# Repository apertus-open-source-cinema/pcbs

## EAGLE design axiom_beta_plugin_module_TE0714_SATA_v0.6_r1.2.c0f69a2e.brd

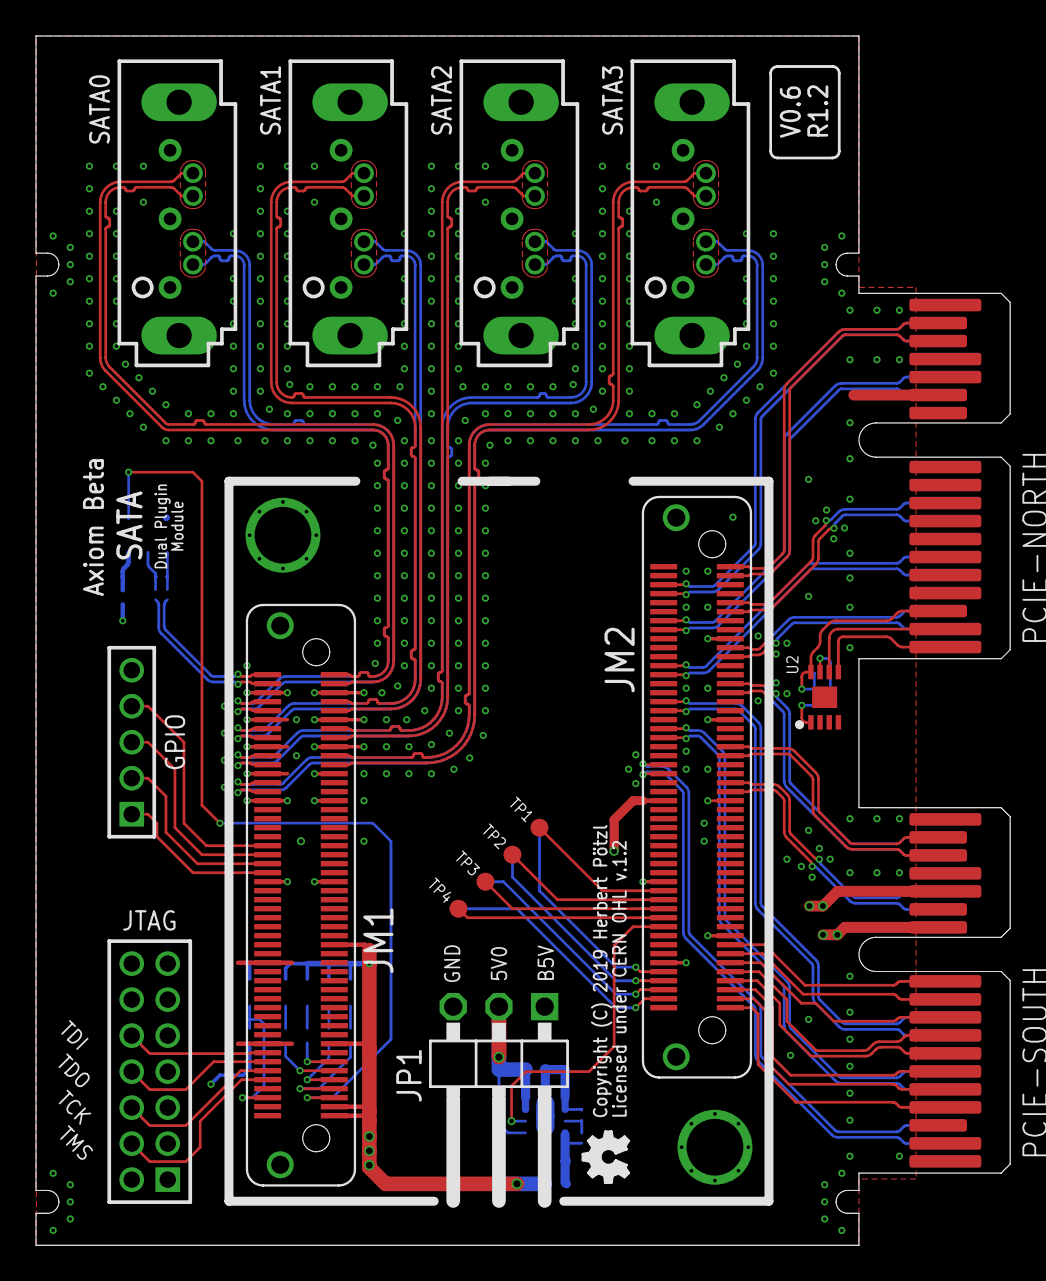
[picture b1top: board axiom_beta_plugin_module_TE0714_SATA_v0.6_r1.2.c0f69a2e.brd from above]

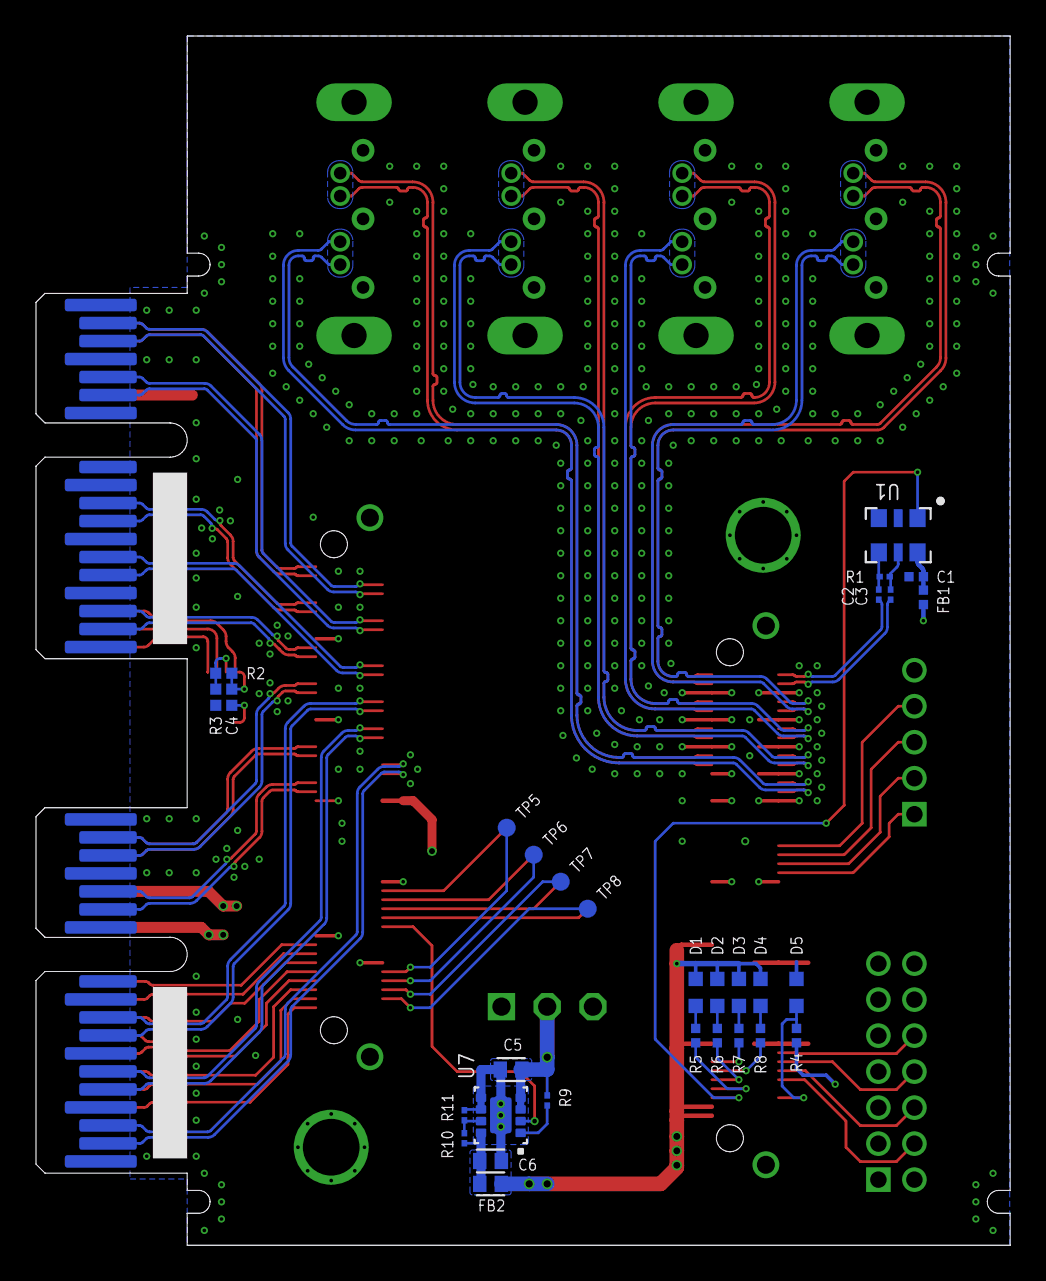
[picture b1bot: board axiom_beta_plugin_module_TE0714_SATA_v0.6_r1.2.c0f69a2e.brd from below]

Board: 4 copper layers, 54.1 x 67.2 mm, 47 parts (30 on the bottom side), 93 nets.

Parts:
C1: 470n; 0402-C
C2, C3: 100n; 0201-C
C4: 0402-B
C5: 10u; 0603-C
C6: 22u; 0603-C
D1, D2, D3, D4, D5: LED; CHIPLED_0603
FB1: 600R 500mA; 0402-C
FB2: 220R 2.2A; 0603-C
GPIO: MMTM-105-05; 1X05M
JM1, JM2: LSHM-150-XX.X-XX-DV-A-S
JP1: 22-28-8034; 1X03/90-S
JTAG: 87760-1416; 2X07M
LOGO2: OSHW_LOGO_FILLX0100-NT; OSHW_FILLX100_NOTEXT
PCIE-NORTH: PCIE-36-AXIOM
PCIE-SOUTH: PCIE-36-AXIOM
R1: 100R; 0201-C
R2: 10k; 0402-B
R3: 1k; 0402-B
R4: 5k6; 0402-C
R5, R6, R7, R8: 10k; 0402-C
R9: 10k; 0201-C
R10: 510k; 0201-C
R11: 162k; 0201-C
SATA0, SATA1, SATA2, SATA3: 67491-0025; SATA7-VERT-S
TP1, TP2, TP3, TP4, TP5, TP6, TP7, TP8: TPTP10R; TP10R
U1: DSC11XX-3.2X2.5; 3.2X2.5
U2: BR24G04NUX; DFN200X300X100-9N
U7: TPS82085; MICROSIP

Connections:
3V3: D1.A, D2.A, D3.A, D4.A, FB1.1, FB2.2, JM1.61, JM1.83, JM1.97, JM1.99, R4.2
B14_L0: JM2.99, PCIE-SOUTH.B4
B14_L11_N: JM2.74, TP1.TP
B14_L11_P: JM2.76, TP2.TP
B14_L12_P: JM2.82, U7.2
B14_L14_N: JM2.78, TP3.TP
B14_L14_P: JM2.80, TP4.TP
B14_L17_N: JM2.89, PCIE-SOUTH.B9
B14_L17_P: JM2.91, PCIE-SOUTH.B8
B14_L18_N: JM2.85, PCIE-SOUTH.B11
B14_L18_P: JM2.87, PCIE-SOUTH.B10
B14_L19_N: JM2.94, TP6.TP
B14_L19_P: JM2.92, TP5.TP
B14_L20_N: JM2.95, PCIE-SOUTH.B6
B14_L20_P: JM2.93, PCIE-SOUTH.B7
B14_L21_N: JM1.95, U1.1
B14_L21_P: JM1.93, R5.1
B14_L22_N: JM2.96, TP7.TP
B14_L22_P: JM2.98, TP8.TP
B14_L23_N: JM1.89, R8.1
B14_L23_P: JM1.91, R6.1
B14_L24_P: JM1.87, R7.1
B14_L25: JM2.97, PCIE-SOUTH.B5
B15_L1_N: JM2.14, PCIE-NORTH.A14
B15_L1_P: JM2.16, PCIE-NORTH.A13
B15_L5_N: JM2.8, PCIE-NORTH.A16
B15_L5_P: JM2.6, PCIE-NORTH.A17
B15_L6_N: JM2.26, PCIE-NORTH.A5
B15_L6_P: JM2.24, PCIE-NORTH.A6
B15_L7_N: JM2.1, PCIE-NORTH.B17
B15_L7_P: JM2.3, PCIE-NORTH.B16
B15_L10_N: JM2.11, PCIE-NORTH.A8
B15_L10_P: JM2.9, PCIE-NORTH.A9
B15_L12_N: JM2.34, PCIE-SOUTH.A8
B15_L12_P: JM2.32, PCIE-SOUTH.A9
B15_L13_N: JM2.38, PCIE-SOUTH.A6
B15_L13_P: JM2.40, PCIE-SOUTH.A5
B15_L15_N: JM2.19, PCIE-NORTH.A3
B15_L15_P: JM2.21, PCIE-NORTH.A2
B15_L18_N: JM2.27, PCIE-SOUTH.A17
B15_L18_P: JM2.29, PCIE-SOUTH.A16
B15_L19_N: JM2.41, PCIE-SOUTH.B17
B15_L19_P: JM2.43, PCIE-SOUTH.B16
B15_L22_N: JM2.46, PCIE-SOUTH.A3
B15_L22_P: JM2.48, PCIE-SOUTH.A2
B15_L23_N: JM2.51, PCIE-SOUTH.A13
B15_L23_P: JM2.49, PCIE-SOUTH.A14
B34_L3_N: GPIO.3, JM1.42
B34_L3_P: GPIO.4, JM1.40
B34_L9_N: GPIO.1, JM1.46
B34_L9_P: GPIO.2, JM1.44
DONE: D5.A, JM1.96, R4.1
EN_B: R9.1, U7.1
FB_B: R10.1, R11.2, U7.7
GND: C1.2, C4.2, C5.2, C6.2, D5.C, GPIO.5, JM1.5, JM1.6, JM1.11, JM1.12, JM1.17, JM1.18, JM1.23, JM1.24, JM1.29, JM1.30, JM1.47, JM1.48, JM1.66, JM1.84, JM1.98, JM1.100, JM1.F1, JM1.F2, JM2.17, JM2.35, JM2.36, JM2.72, JM2.83, JM2.90, JM2.F1, JM2.F2, JP1.3, JTAG.1, JTAG.3, JTAG.5, JTAG.7, JTAG.9, JTAG.11, JTAG.13, PCIE-NORTH.A1, PCIE-NORTH.A4, PCIE-NORTH.A7, PCIE-NORTH.A10, PCIE-NORTH.A12, PCIE-NORTH.A15, PCIE-NORTH.A18, PCIE-NORTH.B15, PCIE-NORTH.B18, PCIE-SOUTH.A1, PCIE-SOUTH.A4, PCIE-SOUTH.A7, PCIE-SOUTH.A10, PCIE-SOUTH.A12, PCIE-SOUTH.A15, PCIE-SOUTH.A18, PCIE-SOUTH.B15, PCIE-SOUTH.B18, R3.2, R11.1, SATA0.1, SATA0.4, SATA0.7, SATA1.1, SATA1.4, SATA1.7, SATA2.1, SATA2.4, SATA2.7, SATA3.1, SATA3.4, SATA3.7, U1.3, U2.1, U2.2, U2.3, U2.4, U2.EP, U7.5, U7.6, U7.EP
I2C_V: C4.1, PCIE-NORTH.B3, R2.1, U2.8
MGT_CLK0_N: C3.2, JM1.4
MGT_CLK0_P: C2.2, JM1.2
MGT_RX0_N: JM1.21, SATA3.5
MGT_RX0_P: JM1.19, SATA3.6
MGT_RX1_N: JM1.15, SATA2.5
MGT_RX1_P: JM1.13, SATA2.6
MGT_RX2_N: JM1.9, SATA1.5
MGT_RX2_P: JM1.7, SATA1.6
MGT_RX3_N: JM1.3, SATA0.5
MGT_RX3_P: JM1.1, SATA0.6
MGT_TX0_N: JM1.28, SATA3.3
MGT_TX0_P: JM1.26, SATA3.2
MGT_TX1_N: JM1.22, SATA2.3
MGT_TX1_P: JM1.20, SATA2.2
MGT_TX2_N: JM1.16, SATA1.3
MGT_TX2_P: JM1.14, SATA1.2
MGT_TX3_N: JM1.10, SATA0.3
MGT_TX3_P: JM1.8, SATA0.2
unnamed: D1.C, R5.2
unnamed: D2.C, R6.2
unnamed: D3.C, R7.2
unnamed: D4.C, R8.2
unnamed: R2.2, R3.1, U2.7
OUT_N: C3.1, R1.2, U1.5
OUT_P: C2.1, R1.1, U1.4
SCL: PCIE-NORTH.B2, U2.6
SDA: PCIE-NORTH.B1, U2.5
S_5V: JP1.1, PCIE-SOUTH.B12
S_VCCIO: JM2.54, PCIE-SOUTH.B14
TCK: JM1.90, JTAG.6
TDI: JM1.86, JTAG.10
TDO: JM1.88, JTAG.8
TMS: JM1.92, JTAG.4
VCCIO0: JM2.53, JTAG.2
VOUT_B: C6.1, FB2.1, R10.2, U7.8
VSUP: C5.1, JP1.2, R9.2, U7.3, U7.4
V_CLK: C1.1, FB1.2, U1.6

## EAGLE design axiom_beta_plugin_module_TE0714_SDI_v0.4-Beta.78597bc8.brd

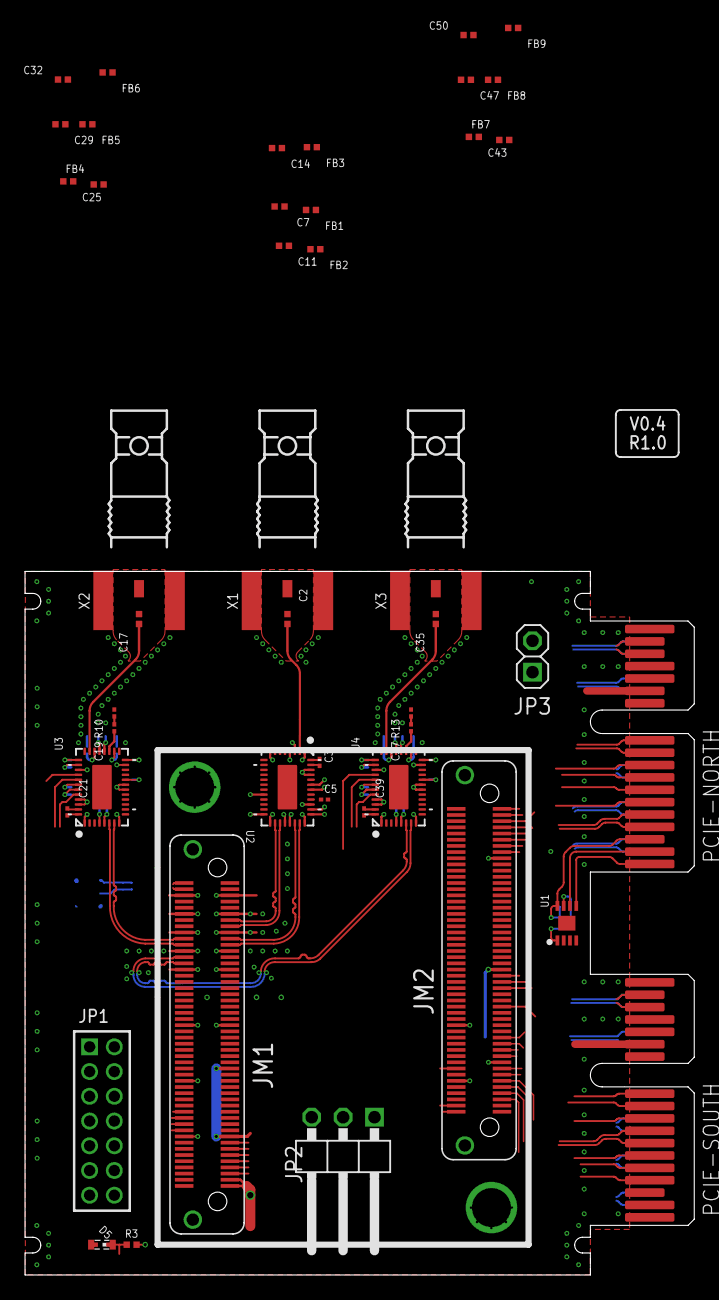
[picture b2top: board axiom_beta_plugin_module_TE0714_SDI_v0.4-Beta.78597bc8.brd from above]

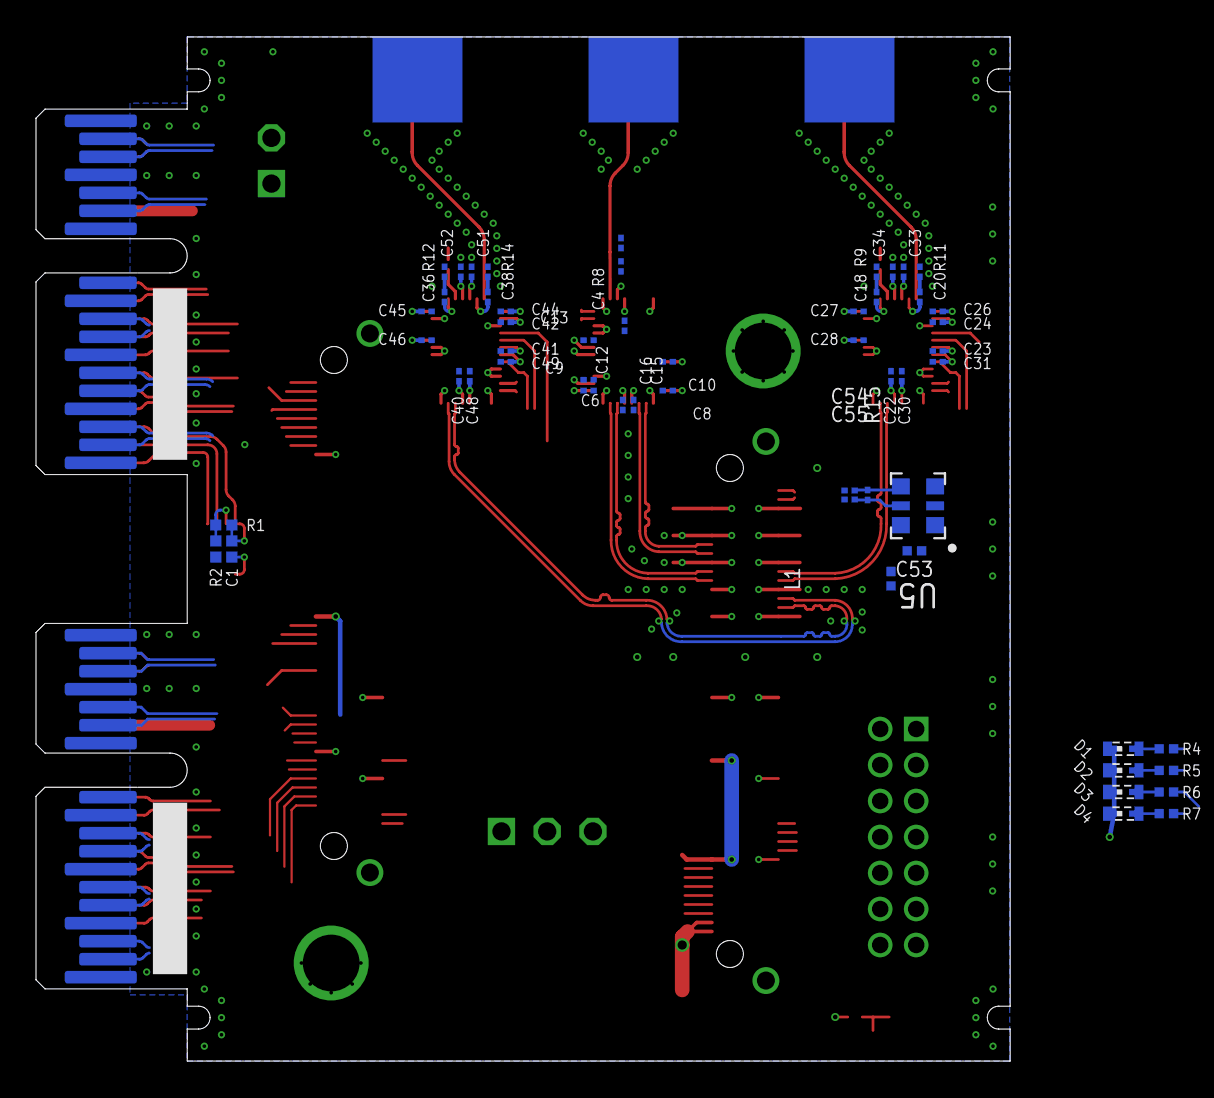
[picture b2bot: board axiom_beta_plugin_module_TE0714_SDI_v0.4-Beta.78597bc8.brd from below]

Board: 4 copper layers, 54.1 x 56.9 mm, 101 parts (56 on the bottom side), 73 nets.

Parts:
C1: 0402-B
C2, C17, C35: 4u7; 0402-C
C3, C21, C39: 470n; 0201-C
C4, C18, C19, C20, C36, C37, C38: 4u7; 0201-C
C5, C6, C12, C23, C24, C30, C41, C42, C48: 10u; 0201-C
C7, C11, C14, C25, C29, C32, C43, C47, C50: 10u; 0402-C
C8, C9, C10, C15, C16, C22, C26, C27, C28, C33, C34, C40, C44, C45, C46, C51, C52, C54, C55: 100n; 0201-C
C13, C31, C49: 1u; 0201-C
C53: 470n; 0402-C
D1, D2, D3, D4, D5: SMARTLED-TTW
FB1, FB2, FB3, FB4, FB5, FB6, FB7, FB8, FB9: 0402-C
JM1, JM2: LSHM-150-XX.X-XX-DV-A-S
JP1: 2X07M
JP2: 1X03/90-S
JP3: 1X02-S
L1: 0402-C
LOGO2: OSHW_LOGO_FILLX0100-NT; OSHW_FILLX100_NOTEXT
PCIE-NORTH: PCIE-36-AXIOM
PCIE-SOUTH: PCIE-36-AXIOM
R1: 10k; 0402-B
R2: 1k; 0402-B
R3, R4, R5, R6, R7: 10k; 0402-C
R8: 0201-C
R9, R10, R11, R12, R13, R14: 75R; 0201-C
R15: 100R; 0201-C
U1: BR24G04NUX; DFN200X300X100-9N
U2: GS12241; UQFN40P600X400X100-41N
U3, U4: GS12281; UQFN40P600X400X100-41N
U5: DSC11XX-3.2X2.5; 3.2X2.5
X1, X2, X3: HDBNC; HDBNC_EDGE_2SIDE

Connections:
1V8: FB1.1, FB2.1, FB3.1, FB4.1, FB5.1, FB7.1, FB8.1, JM2.18
3V3: D1.A@1, D2.A@1, D3.A@1, D4.A@1, FB6.1, FB9.1, JM1.83, L1.1, R3.2
B14_L0: JM2.99, U5.1
B34_L20_N: JM1.76, R4.1
B34_L20_P: JM1.78, R5.1
B34_L24_N: JM1.80, R6.1
B34_L24_P: JM1.82, R7.1
BOOTMODE: JM2.100, JP3.1
DONE: D5.A@1, JM1.96, R3.1
GND: C1.2, C5.2, C6.2, C7.2, C8.2, C9.2, C10.2, C11.2, C12.2, C13.2, C14.2, C15.2, C16.2, C22.2, C23.2, C24.2, C25.2, C26.2, C27.2, C28.2, C29.2, C30.2, C31.2, C32.2, C33.2, C34.2, C40.2, C41.2, C42.2, C43.2, C44.2, C45.2, C46.2, C47.2, C48.2, C49.2, C50.2, C51.2, C52.2, C53.2, D5.C@1, JM1.5, JM1.6, JM1.11, JM1.12, JM1.17, JM1.18, JM1.23, JM1.24, JM1.29, JM1.30, JM1.47, JM1.48, JM1.66, JM1.84, JM1.98, JM1.100, JM1.F1, JM1.F2, JM2.17, JM2.35, JM2.36, JM2.72, JM2.83, JM2.90, JM2.F1, JM2.F2, JP2.1, JP3.2, PCIE-NORTH.A1, PCIE-NORTH.A4, PCIE-NORTH.A7, PCIE-NORTH.A10, PCIE-NORTH.A12, PCIE-NORTH.A15, PCIE-NORTH.A18, PCIE-NORTH.B15, PCIE-NORTH.B18, PCIE-SOUTH.A1, PCIE-SOUTH.A4, PCIE-SOUTH.A7, PCIE-SOUTH.A10, PCIE-SOUTH.A12, PCIE-SOUTH.A15, PCIE-SOUTH.A18, PCIE-SOUTH.B15, PCIE-SOUTH.B18, R2.2, R8.2, R9.2, R10.2, R11.2, R12.2, R13.2, R14.2, U1.1, U1.2, U1.3, U1.4, U1.EP, U2.1, U2.8, U2.14, U2.15, U2.19, U2.21, U2.28, U2.31, U2.37, U2.38, U3.1, U3.8, U3.14, U3.15, U3.19, U3.21, U3.28, U3.31, U3.37, U3.38, U4.1, U4.8, U4.14, U4.15, U4.19, U4.21, U4.28, U4.31, U4.37, U4.38, U5.3, X1.2@1, X1.2@2, X1.2@3, X2.2@1, X2.2@2, X2.2@3, X3.2@1, X3.2@2, X3.2@3
I2C_V: C1.1, PCIE-NORTH.B3, R1.1, U1.8
MGT_RX0_N: JM1.21, U2.27
MGT_RX0_P: JM1.19, U2.26
MGT_RX1_N: JM1.15, U2.23
MGT_RX1_P: JM1.13, U2.22
MGT_TX0_N: JM1.28, U4.6
MGT_TX0_P: JM1.26, U4.7
MGT_TX1_N: JM1.22, U3.6
MGT_TX1_P: JM1.20, U3.7
unnamed: D1.C@1, R4.2
unnamed: D2.C@1, R5.2
unnamed: D3.C@1, R6.2
unnamed: D4.C@1, R7.2
unnamed: C3.2, U2.40
unnamed: C3.1, U2.39
unnamed: C21.2, U3.40
unnamed: C21.1, U3.39
unnamed: C6.1, U2.30
unnamed: C5.1, U2.34
unnamed: C18.2, R9.1
unnamed: C18.1, U3.22
unnamed: C19.1, U3.23
unnamed: C19.2, R10.1
unnamed: C20.1, U3.26
unnamed: C20.2, R11.1
unnamed: C4.2, R8.1
unnamed: C4.1, U2.3
unnamed: C24.1, U3.30
unnamed: C23.1, U3.34
unnamed: C17.1, U3.27
unnamed: C22.1, U3.5
unnamed: C17.2, X2.1
unnamed: C2.2, U2.2
unnamed: C2.1, X1.1
unnamed: C35.1, U4.27
unnamed: C35.2, X3.1
unnamed: C39.2, U4.40
unnamed: C40.1, U4.5
unnamed: C41.1, U4.34
unnamed: C42.1, U4.30
unnamed: C38.2, R14.1
unnamed: C38.1, U4.26
unnamed: C37.2, R13.1
unnamed: C37.1, U4.23
unnamed: C36.1, U4.22
unnamed: C36.2, R12.1
unnamed: C39.1, U4.39
unnamed: R1.2, R2.1, U1.7
OUT_N: C55.1, R15.2, U5.5
OUT_P: C54.1, R15.1, U5.4
SCL: PCIE-NORTH.B2, U1.6
SDA: PCIE-NORTH.B1, U1.5
VCCO_4: C14.1, C15.1, C16.1, FB3.2, U2.24, U2.25
VCCO_8: C32.1, C33.1, C34.1, FB6.2, U3.24, U3.25
VCCO_9: C50.1, C51.1, C52.1, FB9.2, U4.24, U4.25
VCC_4: C11.1, C12.1, C13.1, FB2.2, U2.4, U2.35
VCC_8: C29.1, C30.1, C31.1, FB5.2, U3.4, U3.35
VCC_9: C47.1, C48.1, C49.1, FB8.2, U4.4, U4.35
VDD_4: C7.1, C8.1, C9.1, C10.1, FB1.2, U2.16, U2.20, U2.29
VDD_8: C25.1, C26.1, C27.1, C28.1, FB4.2, U3.16, U3.20, U3.29
VDD_9: C43.1, C44.1, C45.1, C46.1, FB7.2, U4.16, U4.20, U4.29
VIN: JM1.97, JM1.99, JP2.2
VXX: C53.1, L1.2, U5.6

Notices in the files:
axiom_beta_plugin_module_TE0714_SATA_v0.6_r1.2.c0f69a2e.brd:
Copyright (C) 2019 Herbert Pötzl
Licensed under CERN OHL v.1.2
axiom_beta_plugin_module_TE0714_SDI_v0.4-Beta.78597bc8.brd:
Copyright (C) 2017 Herbert Pötzl
